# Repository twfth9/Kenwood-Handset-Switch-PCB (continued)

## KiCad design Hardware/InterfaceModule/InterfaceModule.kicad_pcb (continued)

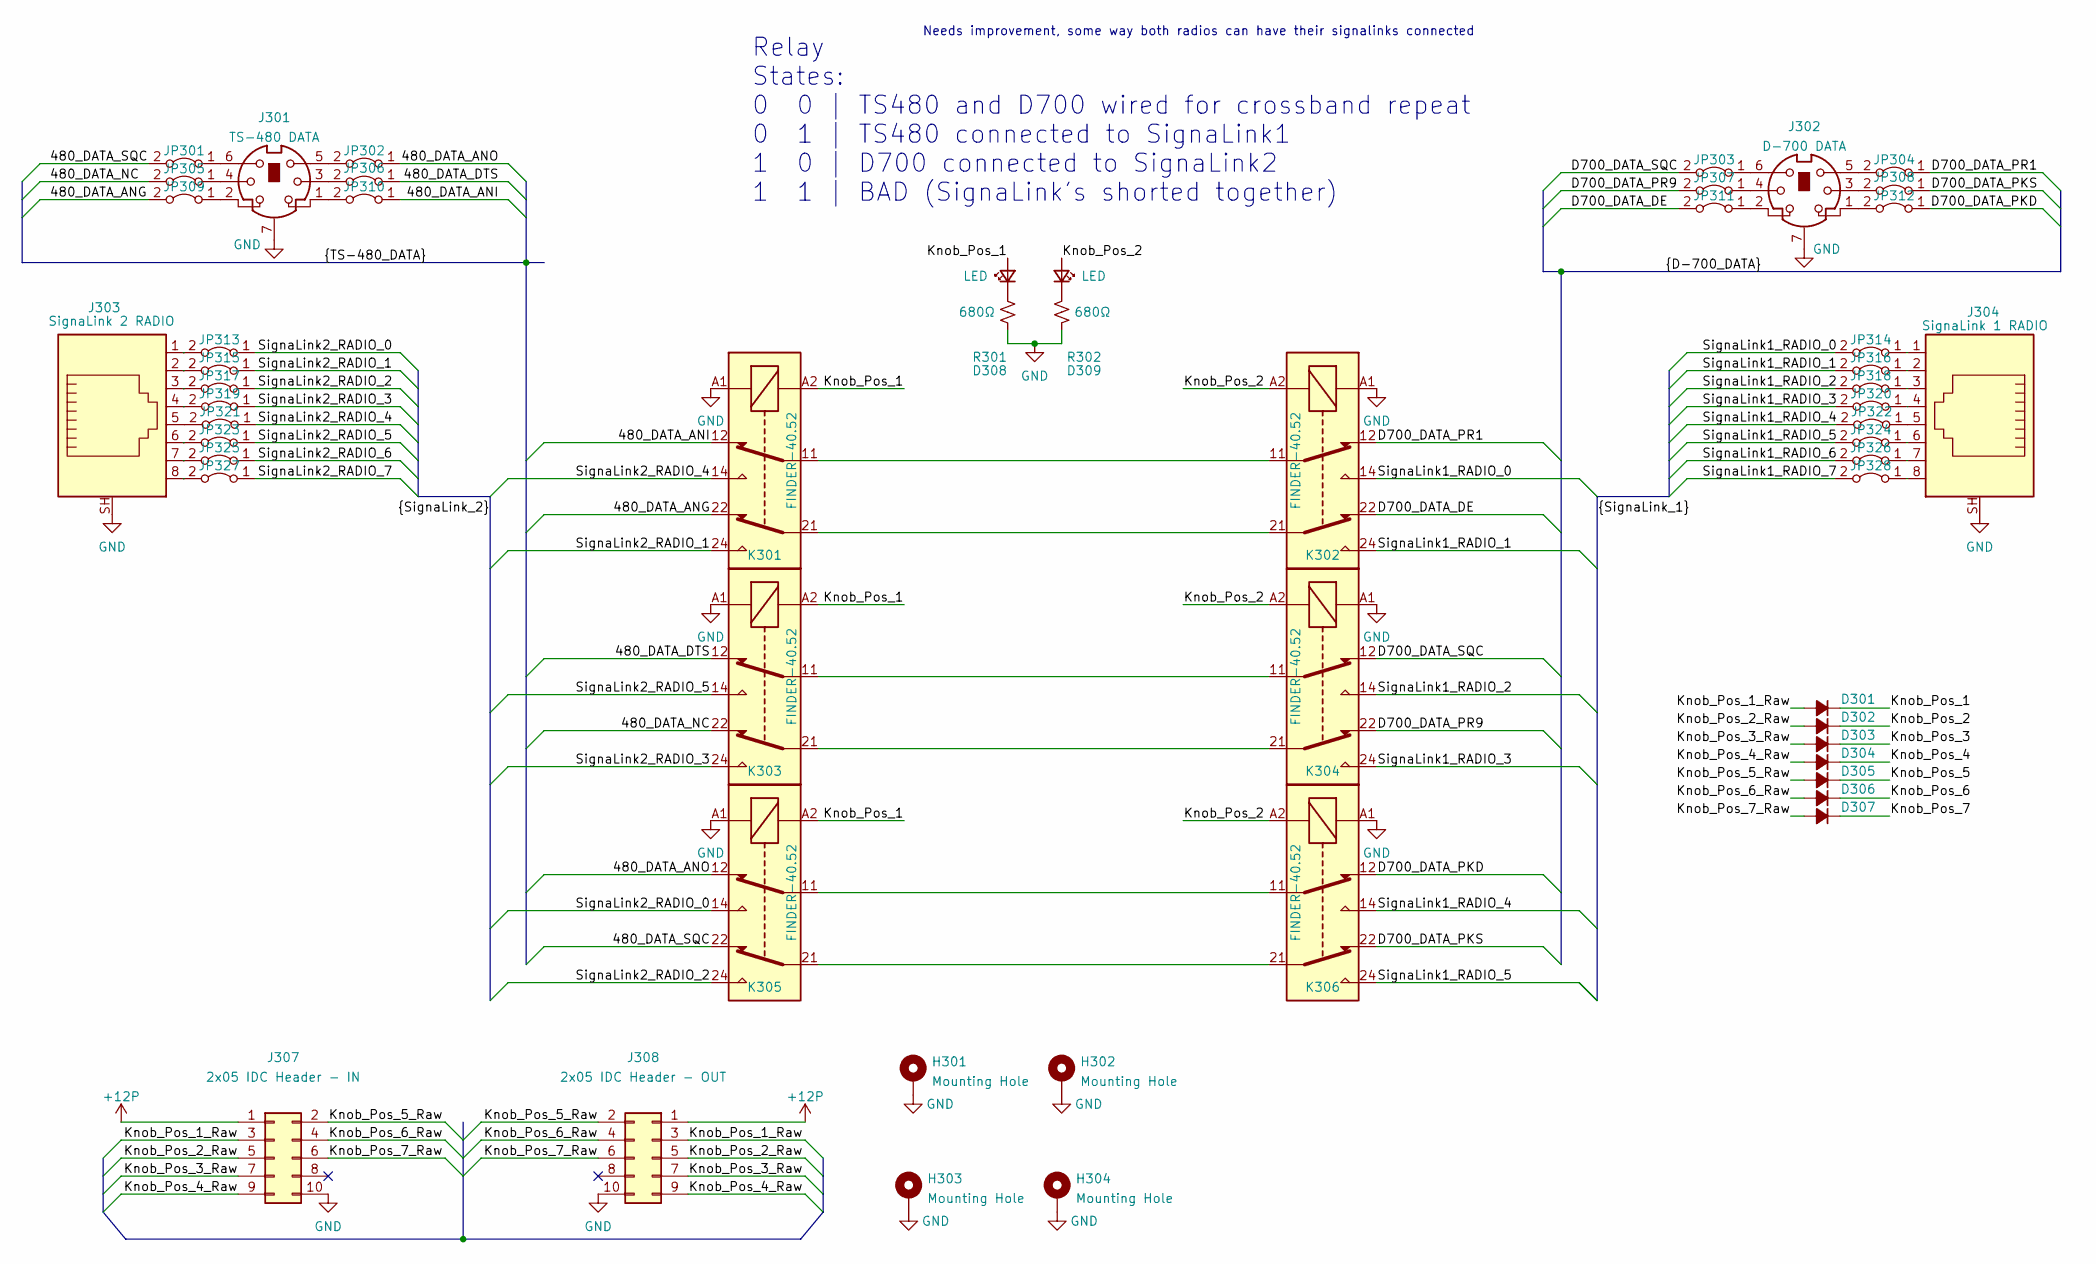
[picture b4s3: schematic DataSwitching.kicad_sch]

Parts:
D301, D302, D303, D304, D305, D306, D307: D_Small_Filled; D_A-405_P2.54mm_Vertical_AnodeUp
D308, D309: LED; LED_D3.0mm
H301, H302, H303, H304: Mounting Hole; M3_Mounting
J301: TS-480 DATA; Connector_Mini-DIN_Female_6Pin_2rows
J302: D-700 DATA; Connector_Mini-DIN_Female_6Pin_2rows
J303: SignaLink 2 RADIO; Mystery_RJ45
J304: SignaLink 1 RADIO; Mystery_RJ45
J307: 2x05 IDC Header - IN; IDC-Header_2x05_P2.54mm_Vertical
J308: 2x05 IDC Header - OUT; IDC-Header_2x05_P2.54mm_Vertical
JP301, JP302, JP303, JP304, JP305, JP306, JP307, JP308, JP309, JP310, JP311, JP312, JP313, JP314, JP315, JP316, JP317, JP318, JP319, JP320, JP321, JP322, JP323, JP324, JP325, JP326, JP327, JP328: Jumper_2_Bridged; 1.0mm_Bridge
K301, K302, K303, K304, K305, K306: FINDER-40.52; Relay_DPDT_Finder_30.22
R301, R302: 680Ω; R_Axial_DIN0207_L6.3mm_D2.5mm_P2.54mm_Vertical

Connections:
+12P: J307.1, J308.1; also elsewhere on the board
/Data Port Switching/480_DATA_ANG: JP309.2 (B), K301.22
/Data Port Switching/480_DATA_ANI: JP310.1 (A), K301.12
/Data Port Switching/480_DATA_ANO: JP302.1 (A), K305.12
/Data Port Switching/480_DATA_DTS: JP306.1 (A), K303.12
/Data Port Switching/480_DATA_NC: JP305.2 (B), K303.22
/Data Port Switching/480_DATA_SQC: JP301.2 (B), K305.22
/Data Port Switching/D700_DATA_DE: JP311.2 (B), K302.22
/Data Port Switching/D700_DATA_PKD: JP312.1 (A), K306.12
/Data Port Switching/D700_DATA_PKS: JP308.1 (A), K306.22
/Data Port Switching/D700_DATA_PR1: JP304.1 (A), K302.12
/Data Port Switching/D700_DATA_PR9: JP307.2 (B), K304.22
/Data Port Switching/D700_DATA_SQC: JP303.2 (B), K304.12
/Data Port Switching/Knob_Pos_1: D301.1 (K), D308.2 (A), K301.A2, K303.A2, K305.A2
/Data Port Switching/Knob_Pos_1_Raw: D301.2 (A), J307.3, J308.3
/Data Port Switching/Knob_Pos_2: D302.1 (K), D309.2 (A), K302.A2, K304.A2, K306.A2
/Data Port Switching/Knob_Pos_2_Raw: D302.2 (A), J307.5, J308.5
/Data Port Switching/Knob_Pos_3: D303.1 (K)
/Data Port Switching/Knob_Pos_3_Raw: D303.2 (A), J307.7, J308.7
/Data Port Switching/Knob_Pos_4: D304.1 (K)
/Data Port Switching/Knob_Pos_4_Raw: D304.2 (A), J307.9, J308.9
/Data Port Switching/Knob_Pos_5: D305.1 (K)
/Data Port Switching/Knob_Pos_5_Raw: D305.2 (A), J307.2, J308.2
/Data Port Switching/Knob_Pos_6: D306.1 (K)
/Data Port Switching/Knob_Pos_6_Raw: D306.2 (A), J307.4, J308.4
/Data Port Switching/Knob_Pos_7: D307.1 (K)
/Data Port Switching/Knob_Pos_7_Raw: D307.2 (A), J307.6, J308.6
/Data Port Switching/SignaLink1_RADIO_0: JP314.2 (B), K302.14
/Data Port Switching/SignaLink1_RADIO_1: JP316.2 (B), K302.24
/Data Port Switching/SignaLink1_RADIO_2: JP318.2 (B), K304.14
/Data Port Switching/SignaLink1_RADIO_3: JP320.2 (B), K304.24
/Data Port Switching/SignaLink1_RADIO_4: JP322.2 (B), K306.14
/Data Port Switching/SignaLink1_RADIO_5: JP324.2 (B), K306.24
/Data Port Switching/SignaLink1_RADIO_6: JP326.2 (B)
/Data Port Switching/SignaLink1_RADIO_7: JP328.2 (B)
/Data Port Switching/SignaLink2_RADIO_0: JP313.1 (A), K305.14
/Data Port Switching/SignaLink2_RADIO_1: JP315.1 (A), K301.24
/Data Port Switching/SignaLink2_RADIO_2: JP317.1 (A), K305.24
/Data Port Switching/SignaLink2_RADIO_3: JP319.1 (A), K303.24
/Data Port Switching/SignaLink2_RADIO_4: JP321.1 (A), K301.14
/Data Port Switching/SignaLink2_RADIO_5: JP323.1 (A), K303.14
/Data Port Switching/SignaLink2_RADIO_6: JP325.1 (A)
/Data Port Switching/SignaLink2_RADIO_7: JP327.1 (A)
GND: H301.1, H302.1, H303.1, H304.1, J301.7, J302.7, J303.SH, J304.SH, J307.10, J308.10, K301.A1, K302.A1, K303.A1, K304.A1, K305.A1, K306.A1, R301.2, R302.2; also elsewhere on the board
unnamed: D308.1 (K), R301.1
unnamed: D309.1 (K), R302.1
unnamed: J301.1, JP310.2 (B)
unnamed: J301.2, JP309.1 (A)
unnamed: J301.3, JP306.2 (B)
unnamed: J301.5, JP302.2 (B)
unnamed: J301.6, JP301.1 (A)
unnamed: J302.1, JP312.2 (B)
unnamed: J302.2, JP311.1 (A)
unnamed: J302.3, JP308.2 (B)
unnamed: J302.4, JP307.1 (A)
unnamed: J302.5, JP304.2 (B)
unnamed: J302.6, JP303.1 (A)
unnamed: J303.6, JP323.2 (B)
unnamed: J304.1, JP314.1 (A)
unnamed: J304.2, JP316.1 (A)
unnamed: J304.3, JP318.1 (A)
unnamed: J304.4, JP320.1 (A)
unnamed: J304.6, JP324.1 (A)
unnamed: J304.7, JP326.1 (A)
unnamed: J304.8, JP328.1 (A)
unnamed: J301.4, JP305.1 (A)
unnamed: J303.1, JP313.2 (B)
unnamed: J303.2, JP315.2 (B)
unnamed: J303.3, JP317.2 (B)
unnamed: J303.4, JP319.2 (B)
unnamed: J303.5, JP321.2 (B)
unnamed: J304.5, JP322.1 (A)
unnamed: J303.7, JP325.2 (B)
unnamed: J303.8, JP327.2 (B)
unnamed: K301.11, K302.11
unnamed: K301.21, K302.21
unnamed: K303.11, K304.11
unnamed: K303.21, K304.21
unnamed: K305.11, K306.11
unnamed: K305.21, K306.21

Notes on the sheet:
Relay States: 0 0 | TS480 and D700 wired for crossband repeat 0 1 | TS480 connected to SignaLink1 1 0 | D700 connected to SignaLink2 1 1 | BAD (SignaLink's shorted together)
Needs improvement, some way both radios can have their signalinks connected

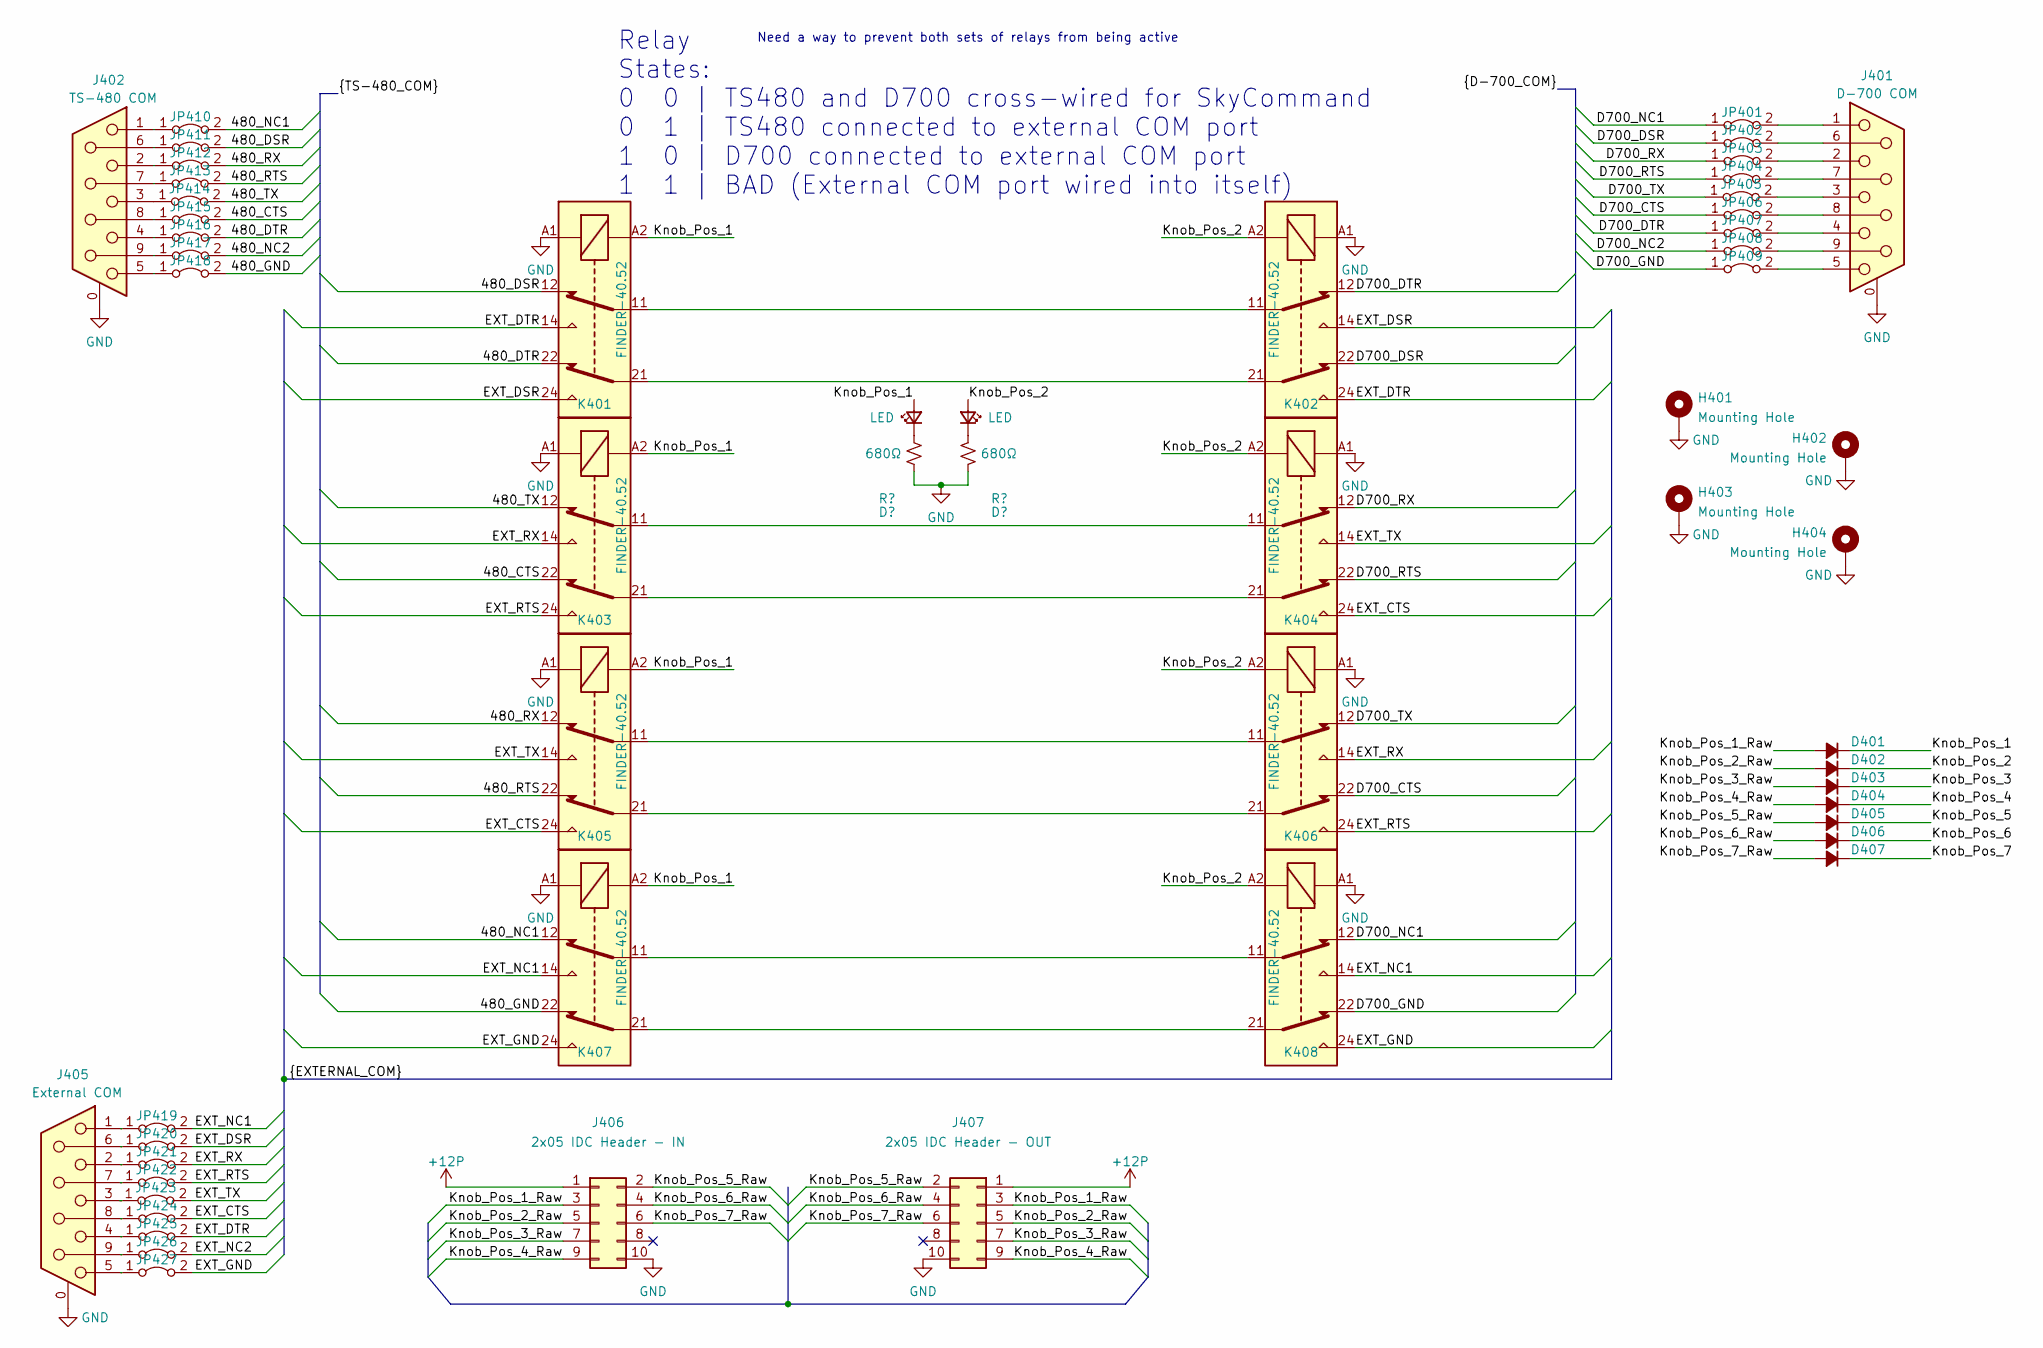
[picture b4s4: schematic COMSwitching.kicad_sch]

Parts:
D401, D402, D403, D404, D405, D406, D407: D_Small_Filled; D_A-405_P2.54mm_Vertical_AnodeUp
H401, H402, H403, H404: Mounting Hole; M3_Mounting
J401: D-700 COM; DSUB-9_Male_Horizontal_P2.77x2.84mm_EdgePinOffset7.70mm_Hou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
J402: TS-480 COM; DSUB-9_Male_Horizontal_P2.77x2.84mm_EdgePinOffset7.70mm_Hou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
J405: External COM; DSUB-9_Male_Horizontal_P2.77x2.84mm_EdgePinOffset7.70mm_Hou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
J406: 2x05 IDC Header - IN; IDC-Header_2x05_P2.54mm_Vertical
J407: 2x05 IDC Header - OUT; IDC-Header_2x05_P2.54mm_Vertical
JP401, JP402, JP403, JP404, JP405, JP406, JP407, JP408, JP409, JP410, JP411, JP412, JP413, JP414, JP415, JP416, JP417, JP418, JP419, JP420, JP421, JP422, JP423, JP424, JP425, JP426, JP427: Jumper_2_Bridged; 1.0mm_Bridge
K401, K402, K403, K404, K405, K406, K407, K408: FINDER-40.52; Relay_DPDT_Finder_30.22

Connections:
+12P: J406.1, J407.1; also elsewhere on the board
/COM Port Switching/480_CTS: JP415.2 (B), K403.22
/COM Port Switching/480_DSR: JP411.2 (B), K401.12
/COM Port Switching/480_DTR: JP416.2 (B), K401.22
/COM Port Switching/480_GND: JP418.2 (B), K407.22
/COM Port Switching/480_NC1: JP410.2 (B), K407.12
/COM Port Switching/480_NC2: JP417.2 (B)
/COM Port Switching/480_RTS: JP413.2 (B), K405.22
/COM Port Switching/480_RX: JP412.2 (B), K405.12
/COM Port Switching/480_TX: JP414.2 (B), K403.12
/COM Port Switching/D700_CTS: JP406.1 (A), K406.22
/COM Port Switching/D700_DSR: JP402.1 (A), K402.22
/COM Port Switching/D700_DTR: JP407.1 (A), K402.12
/COM Port Switching/D700_GND: JP409.1 (A), K408.22
/COM Port Switching/D700_NC1: JP401.1 (A), K408.12
/COM Port Switching/D700_NC2: JP408.1 (A)
/COM Port Switching/D700_RTS: JP404.1 (A), K404.22
/COM Port Switching/D700_RX: JP403.1 (A), K404.12
/COM Port Switching/D700_TX: JP405.1 (A), K406.12
/COM Port Switching/EXT_CTS: JP424.2 (B), K404.24, K405.24
/COM Port Switching/EXT_DSR: JP420.2 (B), K401.24, K402.14
/COM Port Switching/EXT_DTR: JP425.2 (B), K401.14, K402.24
/COM Port Switching/EXT_GND: JP427.2 (B), K407.24, K408.24
/COM Port Switching/EXT_NC1: JP419.2 (B), K407.14, K408.14
/COM Port Switching/EXT_NC2: JP426.2 (B)
/COM Port Switching/EXT_RTS: JP422.2 (B), K403.24, K406.24
/COM Port Switching/EXT_RX: JP421.2 (B), K403.14, K406.14
/COM Port Switching/EXT_TX: JP423.2 (B), K404.14, K405.14
/COM Port Switching/Knob_Pos_1: D401.1 (K), K401.A2, K403.A2, K405.A2, K407.A2
/COM Port Switching/Knob_Pos_1_Raw: D401.2 (A), J406.3, J407.3
/COM Port Switching/Knob_Pos_2: D402.1 (K), K402.A2, K404.A2, K406.A2, K408.A2
/COM Port Switching/Knob_Pos_2_Raw: D402.2 (A), J406.5, J407.5
/COM Port Switching/Knob_Pos_3: D403.1 (K)
/COM Port Switching/Knob_Pos_3_Raw: D403.2 (A), J406.7, J407.7
/COM Port Switching/Knob_Pos_4: D404.1 (K)
/COM Port Switching/Knob_Pos_4_Raw: D404.2 (A), J406.9, J407.9
/COM Port Switching/Knob_Pos_5: D405.1 (K)
/COM Port Switching/Knob_Pos_5_Raw: D405.2 (A), J406.2, J407.2
/COM Port Switching/Knob_Pos_6: D406.1 (K)
/COM Port Switching/Knob_Pos_6_Raw: D406.2 (A), J406.4, J407.4
/COM Port Switching/Knob_Pos_7: D407.1 (K)
/COM Port Switching/Knob_Pos_7_Raw: D407.2 (A), J406.6, J407.6
GND: H401.1, H402.1, H403.1, H404.1, J401.0 (PAD), J402.0 (PAD), J405.0 (PAD), J406.10, J407.10, K401.A1, K402.A1, K403.A1, K404.A1, K405.A1, K406.A1, K407.A1, K408.A1; also elsewhere on the board
unnamed: J401.1, JP401.2 (B)
unnamed: J401.2, JP403.2 (B)
unnamed: J401.3, JP405.2 (B)
unnamed: J401.4, JP407.2 (B)
unnamed: J401.5, JP409.2 (B)
unnamed: J401.6, JP402.2 (B)
unnamed: J401.7, JP404.2 (B)
unnamed: J401.8, JP406.2 (B)
unnamed: J401.9, JP408.2 (B)
unnamed: J402.1, JP410.1 (A)
unnamed: J402.2, JP412.1 (A)
unnamed: J402.3, JP414.1 (A)
unnamed: J402.4, JP416.1 (A)
unnamed: J402.5, JP418.1 (A)
unnamed: J402.6, JP411.1 (A)
unnamed: J402.7, JP413.1 (A)
unnamed: J402.8, JP415.1 (A)
unnamed: J402.9, JP417.1 (A)
unnamed: J405.1, JP419.1 (A)
unnamed: J405.2, JP421.1 (A)
unnamed: J405.3, JP423.1 (A)
unnamed: J405.4, JP425.1 (A)
unnamed: J405.5, JP427.1 (A)
unnamed: J405.6, JP420.1 (A)
unnamed: J405.7, JP422.1 (A)
unnamed: J405.8, JP424.1 (A)
unnamed: J405.9, JP426.1 (A)
unnamed: K401.11, K402.11
unnamed: K401.21, K402.21
unnamed: K403.11, K404.11
unnamed: K403.21, K404.21
unnamed: K405.11, K406.11
unnamed: K405.21, K406.21
unnamed: K407.11, K408.11
unnamed: K407.21, K408.21

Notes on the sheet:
Need a way to prevent both sets of relays from being active
Relay States: 0 0 | TS480 and D700 cross-wired for SkyCommand 0 1 | TS480 connected to external COM port 1 0 | D700 connected to external COM port 1 1 | BAD (External COM port wired into itself)

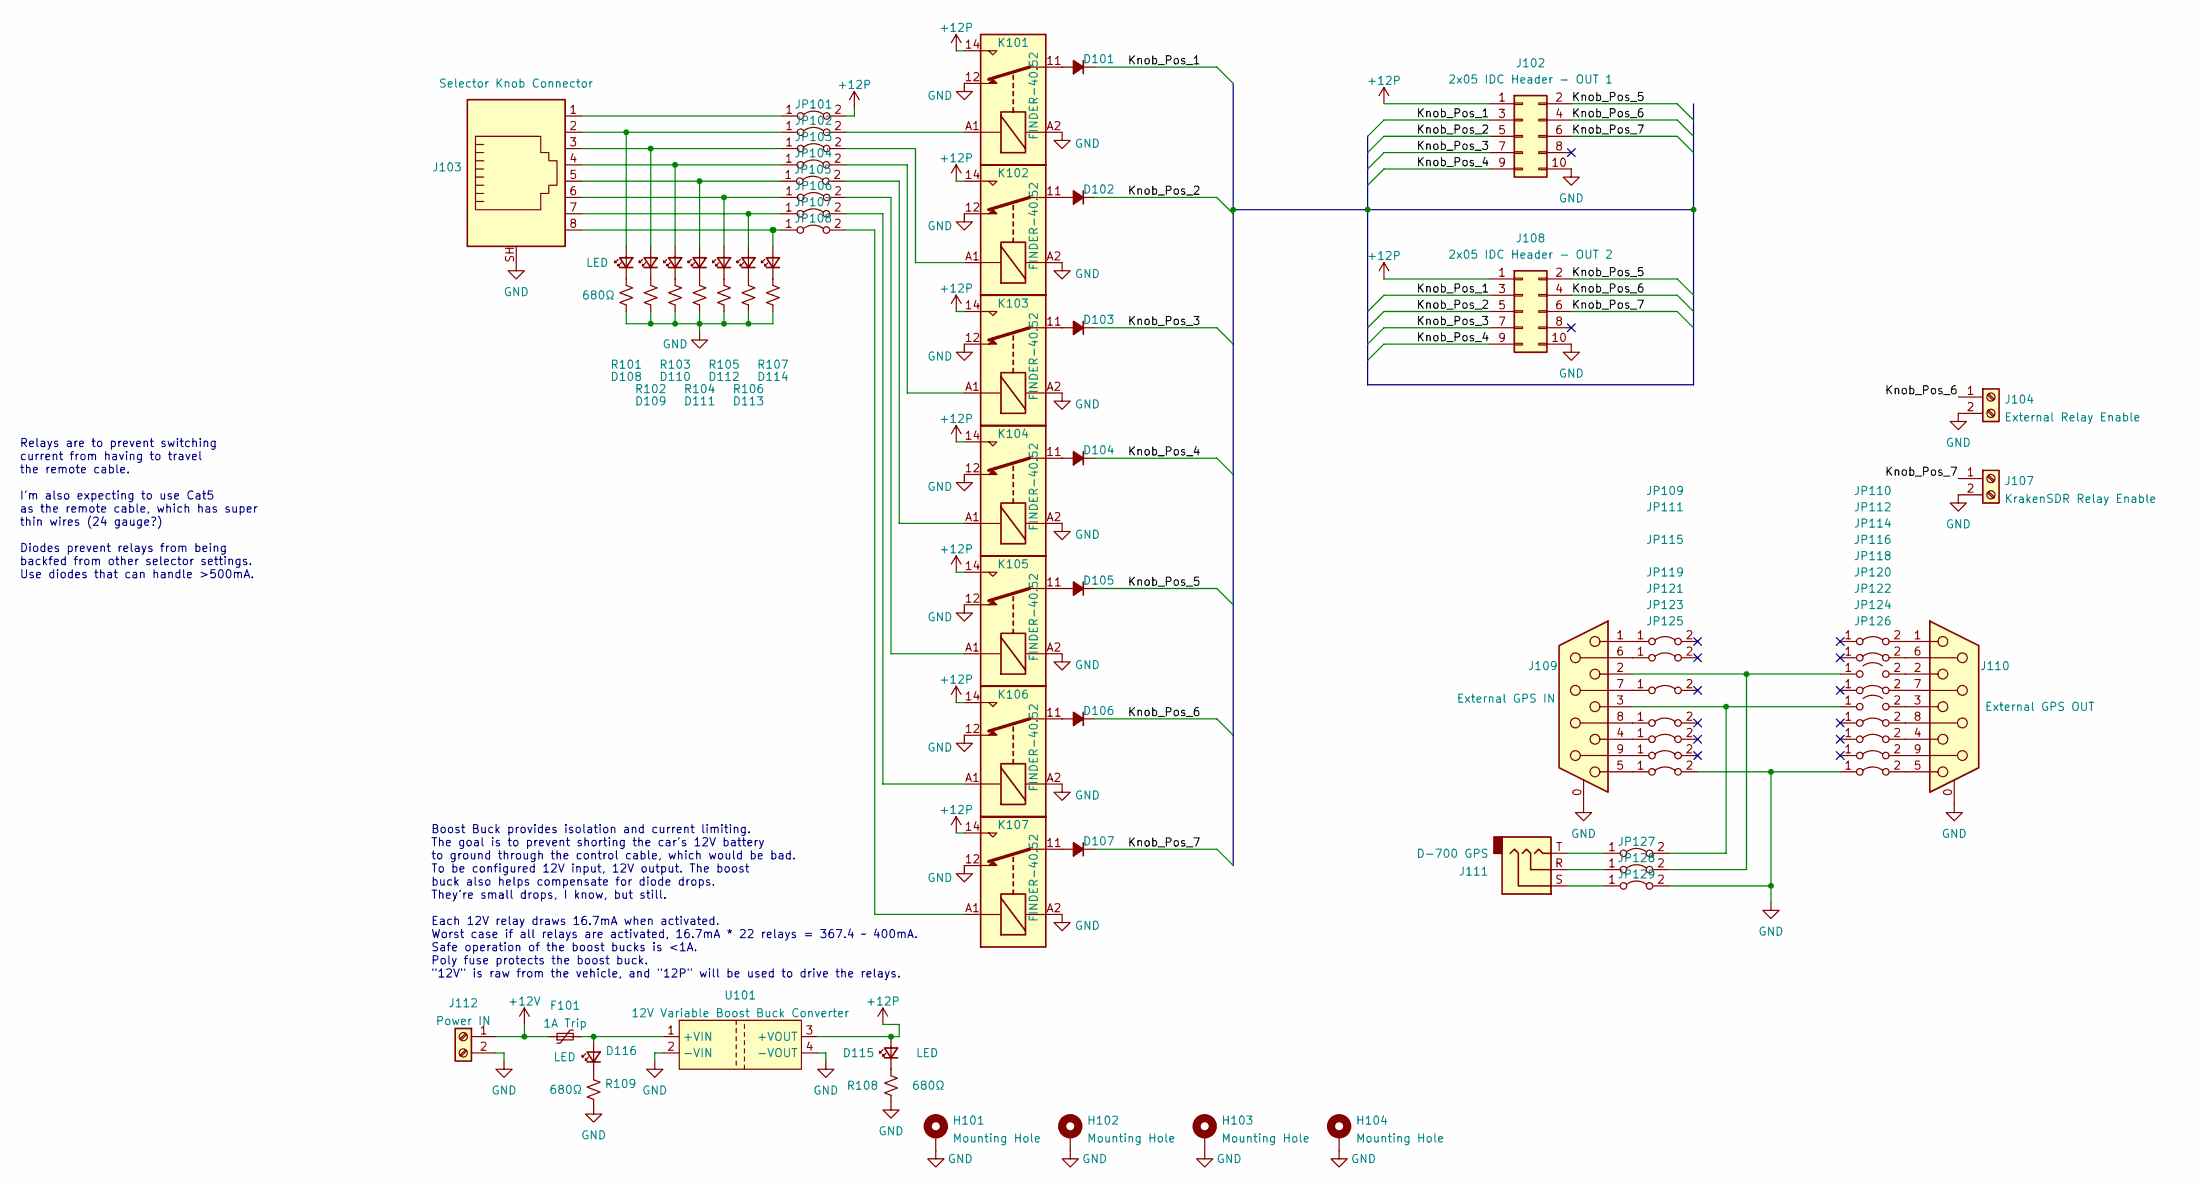
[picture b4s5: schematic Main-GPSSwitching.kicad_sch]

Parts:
D101, D102, D103, D104, D105, D106, D107: D_Small_Filled; D_A-405_P2.54mm_Vertical_AnodeUp
D108, D109, D110, D111, D112, D113, D114, D115, D116: LED; LED_D3.0mm
F101: 1A Trip; Fuse_Bourns_MF-RG300
H101, H102, H103, H104: Mounting Hole; M3_Mounting
J102: 2x05 IDC Header - OUT 1; IDC-Header_2x05_P2.54mm_Vertical
J103: Selector Knob Connector; Mystery_RJ45
J104: External Relay Enable; TerminalBlock_Phoenix_MKDS-1,5-2_1x02_P5.00mm_Horizontal
J107: KrakenSDR Relay Enable; TerminalBlock_Phoenix_MKDS-1,5-2_1x02_P5.00mm_Horizontal
J108: 2x05 IDC Header - OUT 2; IDC-Header_2x05_P2.54mm_Vertical
J109: External GPS IN; DSUB-9_Male_Horizontal_P2.77x2.84mm_EdgePinOffset7.70mm_Hou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
J110: External GPS OUT; DSUB-9_Male_Horizontal_P2.77x2.84mm_EdgePinOffset7.70mm_Hou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
J111: D-700 GPS; Mystery_3.5mm
J112: Power IN; TerminalBlock_Phoenix_MKDS-1,5-2_1x02_P5.00mm_Horizontal
JP101, JP102, JP103, JP104, JP105, JP106, JP107, JP108, JP109, JP110, JP111, JP112, JP115, JP116, JP119, JP120, JP121, JP122, JP123, JP124, JP125, JP126, JP127, JP128, JP129: Jumper_2_Bridged; 1.0mm_Bridge
JP114, JP118: Jumper_2_Bridged; 1.0mm_Bridge_Open
K101, K102, K103, K104, K105, K106, K107: FINDER-40.52; Relay_DPDT_Finder_30.22
R101, R102, R103, R104, R105, R106, R107, R108, R109: 680Ω; R_Axial_DIN0207_L6.3mm_D2.5mm_P2.54mm_Vertical
U101: 12V Variable Boost Buck Converter; BoostBuck

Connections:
+12P: D115.2 (A), J102.1, J108.1, JP101.2 (B), K101.14, K102.14, K103.14, K104.14, K105.14, K106.14, K107.14, U101.3 (+VOUT); also elsewhere on the board
+12V: F101.1, J112.1
/Main & GPS Switching/Knob_Pos_1: D101.1 (K), J102.3, J108.3
/Main & GPS Switching/Knob_Pos_2: D102.1 (K), J102.5, J108.5
/Main & GPS Switching/Knob_Pos_3: D103.1 (K), J102.7, J108.7
/Main & GPS Switching/Knob_Pos_4: D104.1 (K), J102.9, J108.9
/Main & GPS Switching/Knob_Pos_5: D105.1 (K), J102.2, J108.2
/Main & GPS Switching/Knob_Pos_6: D106.1 (K), J102.4, J104.1, J108.4
/Main & GPS Switching/Knob_Pos_7: D107.1 (K), J102.6, J107.1, J108.6
GND: H101.1, H102.1, H103.1, H104.1, J102.10, J103.SH, J104.2, J107.2, J108.10, J109.0 (PAD), J110.0 (PAD), J112.2, JP125.2 (B), JP126.1 (A), JP129.2 (B), K101.12, K101.A2, K102.12, K102.A2, K103.12, K103.A2, K104.12, K104.A2, K105.12, K105.A2, K106.12, K106.A2, K107.12, K107.A2, R101.2, R102.2, R103.2, R104.2, R105.2, R106.2, R107.2, R108.2, R109.2, U101.2 (-VIN), U101.4 (-VOUT); also elsewhere on the board
unnamed: D101.2 (A), K101.11
unnamed: D102.2 (A), K102.11
unnamed: D103.2 (A), K103.11
unnamed: D104.2 (A), K104.11
unnamed: D105.2 (A), K105.11
unnamed: D106.2 (A), K106.11
unnamed: D107.2 (A), K107.11
unnamed: D108.1 (K), R101.1
unnamed: D109.1 (K), R102.1
unnamed: D110.1 (K), R103.1
unnamed: D111.1 (K), R104.1
unnamed: D112.1 (K), R105.1
unnamed: D113.1 (K), R106.1
unnamed: D114.1 (K), R107.1
unnamed: D115.1 (K), R108.1
unnamed: D116.1 (K), R109.1
unnamed: D116.2 (A), F101.2, U101.1 (+VIN)
unnamed: J103.1, JP101.1 (A)
unnamed: D108.2 (A), J103.2, JP102.1 (A)
unnamed: D109.2 (A), J103.3, JP103.1 (A)
unnamed: D110.2 (A), J103.4, JP104.1 (A)
unnamed: D111.2 (A), J103.5, JP105.1 (A)
unnamed: D112.2 (A), J103.6, JP106.1 (A)
unnamed: D113.2 (A), J103.7, JP107.1 (A)
unnamed: D114.2 (A), J103.8, JP108.1 (A)
unnamed: J109.1, JP109.1 (A)
unnamed: J109.4, JP121.1 (A)
unnamed: J109.5, JP125.1 (A)
unnamed: J109.6, JP111.1 (A)
unnamed: J109.7, JP115.1 (A)
unnamed: J109.8, JP119.1 (A)
unnamed: J109.9, JP123.1 (A)
unnamed: J110.1, JP110.2 (B)
unnamed: J110.2, JP114.2 (B)
unnamed: J110.3, JP118.2 (B)
unnamed: J110.4, JP122.2 (B)
unnamed: J110.5, JP126.2 (B)
unnamed: J110.6, JP112.2 (B)
unnamed: J110.7, JP116.2 (B)
unnamed: J110.8, JP120.2 (B)
unnamed: J110.9, JP124.2 (B)
unnamed: J111.S, JP129.1 (A)
unnamed: J111.T, JP127.1 (A)
unnamed: J111.R, JP128.1 (A)
unnamed: JP102.2 (B), K101.A1
unnamed: JP103.2 (B), K102.A1
unnamed: JP104.2 (B), K103.A1
unnamed: JP105.2 (B), K104.A1
unnamed: JP106.2 (B), K105.A1
unnamed: JP107.2 (B), K106.A1
unnamed: JP108.2 (B), K107.A1

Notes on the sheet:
Relays are to prevent switching current from having to travel the remote cable. I'm also expecting to use Cat5 as the remote cable, which has super thin wires (24 gauge?) Diodes prevent relays from being backfed from other selector settings. Use diodes that can handle >500mA.
Boost Buck provides isolation and current limiting. The goal is to prevent shorting the car's 12V battery to ground through the control cable, which would be bad. To be configured 12V input, 12V output. The boost buck also helps compensate for diode drops. They're small drops, I know, but still. Ea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

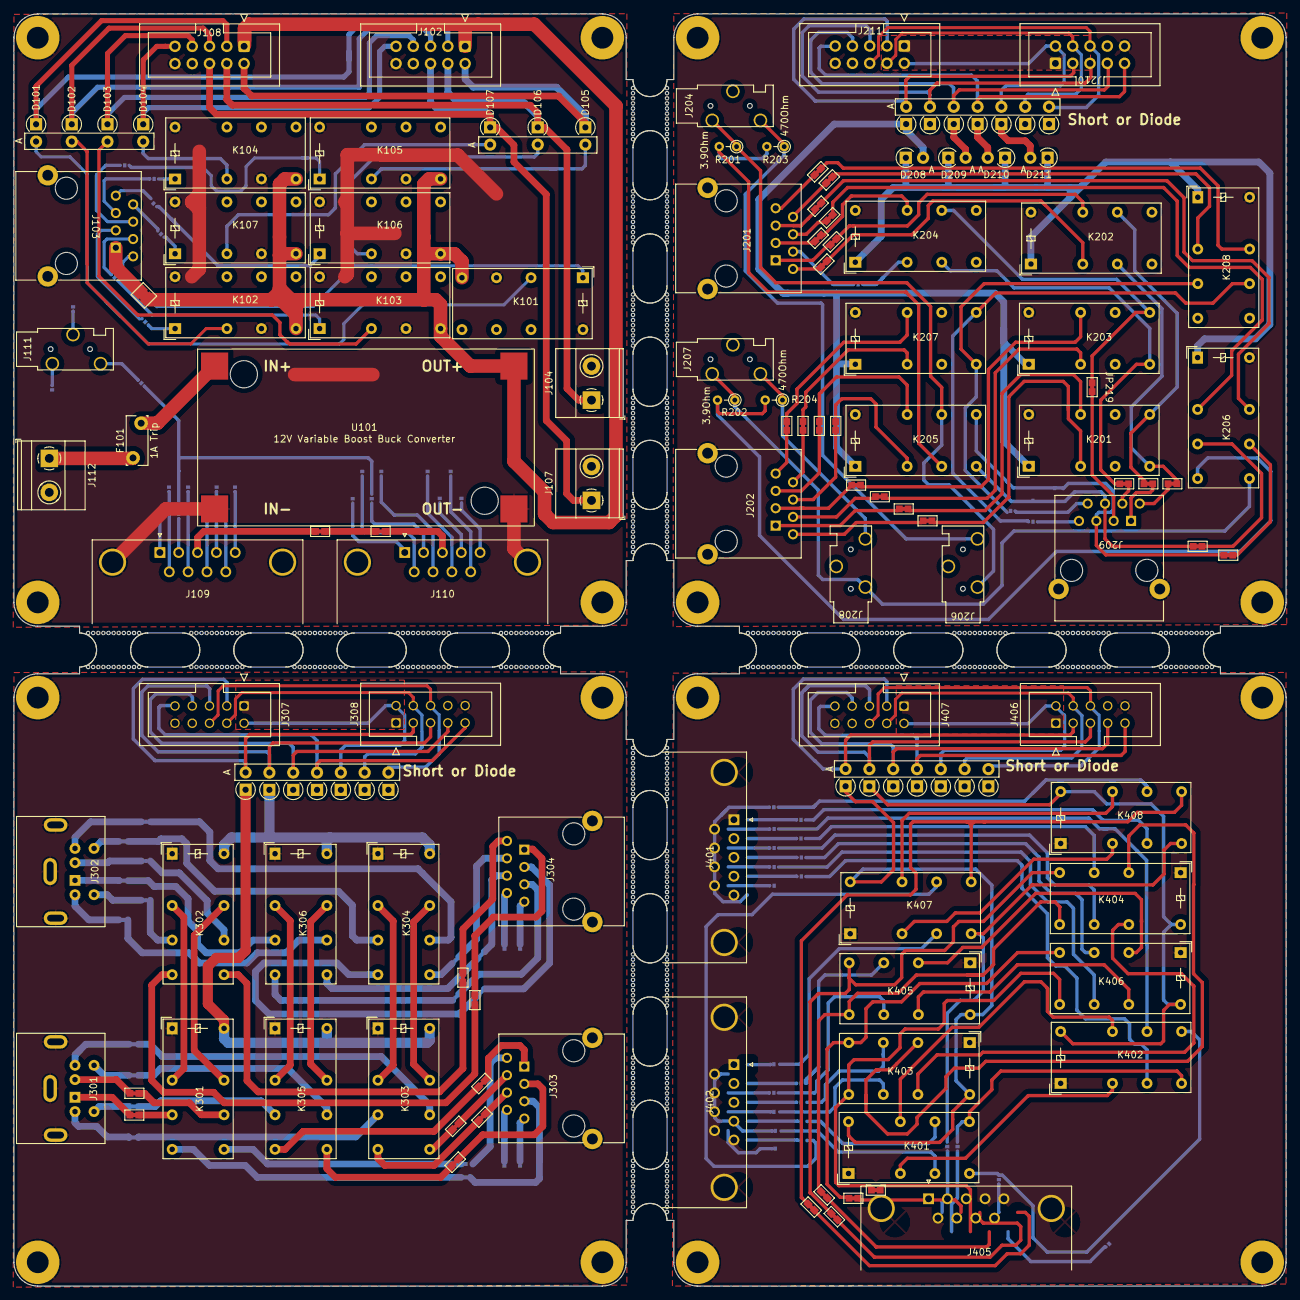
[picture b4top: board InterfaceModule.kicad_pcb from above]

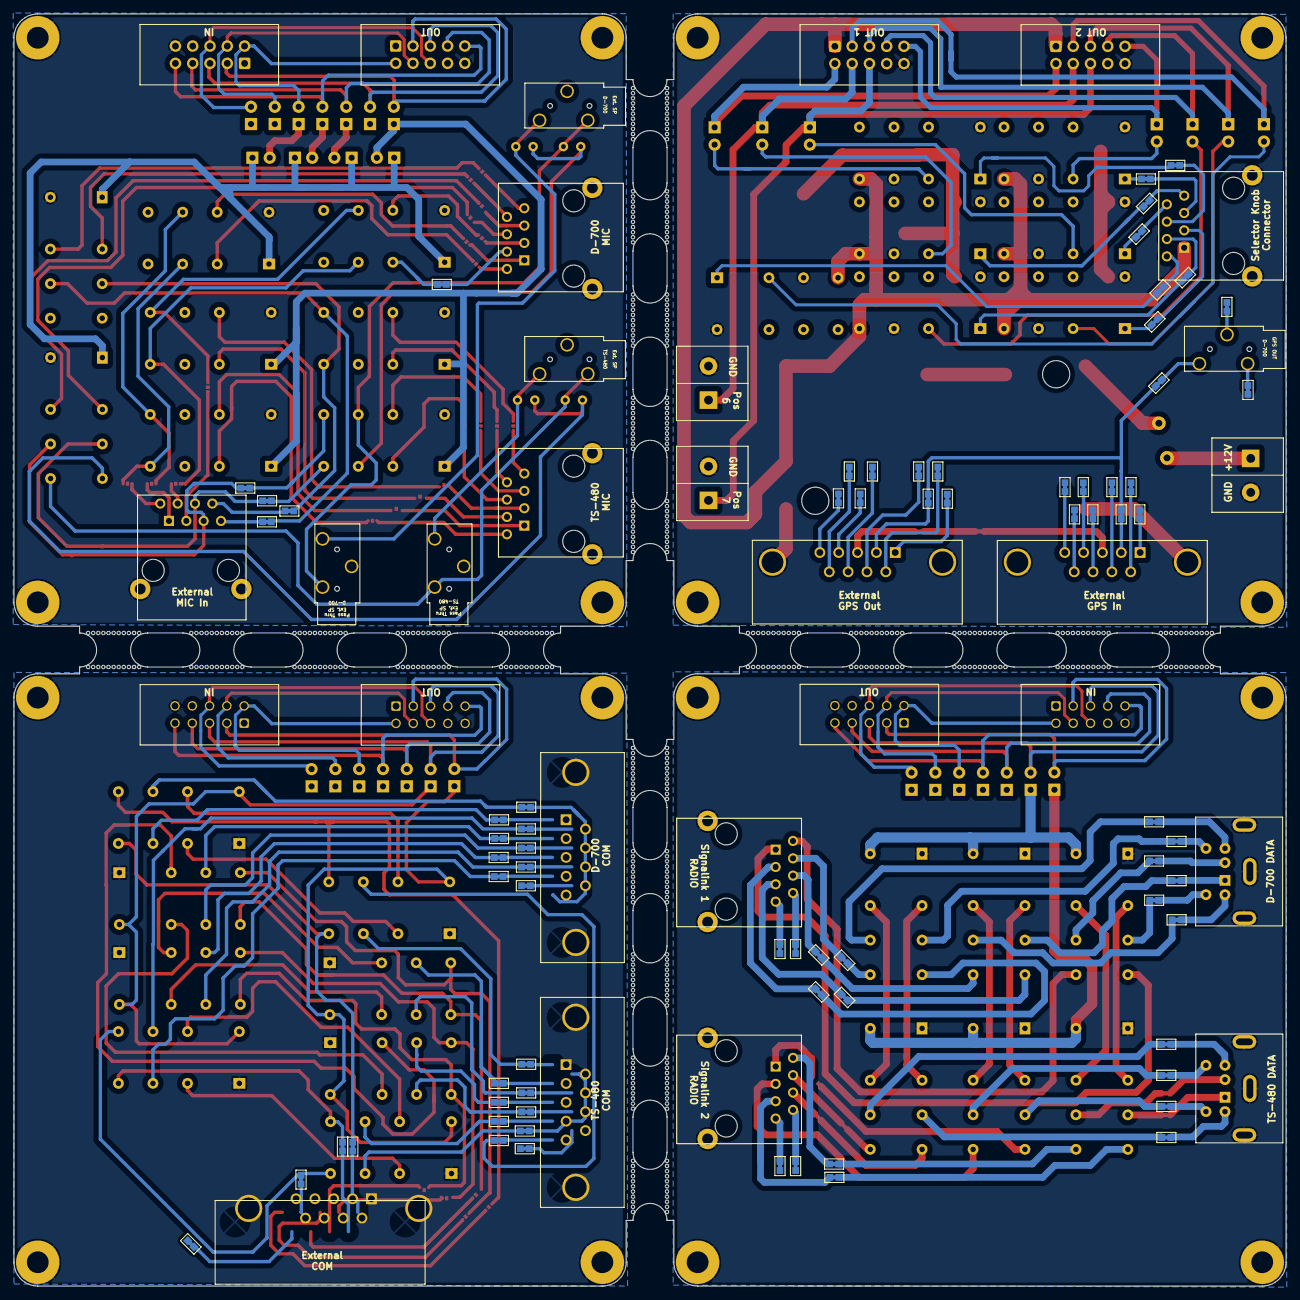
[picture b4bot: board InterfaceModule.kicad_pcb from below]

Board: 2 copper layers, 187.0 x 187.0 mm, 242 parts (73 on the bottom side), 255 nets.

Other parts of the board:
JP113, JP117, JP225, JP225#2, JP225#3, JP225#4: Jumper_2_Bridged; 1.0mm_Bridge
mouse-bite-5mm-slot, mouse-bite-5mm-slot#2, mouse-bite-5mm-slot#3, mouse-bite-5mm-slot#4, mouse-bite-5mm-slot#5, mouse-bite-5mm-slot#6, mouse-bite-5mm-slot#7, mouse-bite-5mm-slot#8, mouse-bite-5mm-slot#9, mouse-bite-5mm-slot#10, mouse-bite-5mm-slot#11, mouse-bite-5mm-slot#12, mouse-bite-5mm-slot#13, mouse-bite-5mm-slot#14, mouse-bite-5mm-slot#15, mouse-bite-5mm-slot#16, mouse-bite-5mm-slot#17, mouse-bite-5mm-slot#18, mouse-bite-5mm-slot#19, mouse-bite-5mm-slot#20: VAL**; mouse-bite-5mm-slot
